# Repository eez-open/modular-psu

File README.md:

### Ownership and License
The contributors are listed in CONTRIB.TXT. 

Licenses | OSHWA UID
--|--
 | 

### Introduction

EEZ Bench Box 3 (BB3) represents a new category of *modular* Test and Measurement (T&M) equipment. It provides a complete open-source hardware and software framework that bridges the gap between – and combines the best features of – DIY hobbyist tools and professional benchtop equipment. 
BB3 was inspired by the [EEZ H24005](https://github.com/eez-open/psu-hw) power supply project ([OSHWA UID HR000001](https://certification.oshwa.org/hr000001.html)), which attracted many enthusiasts with its broad feature-set, rich user interface, DIY-friendliness, and fully open-source design. 
It initially comes with two DC power modules (hence the name of repository *modular-psu*) and will be expanded with new T&M modules (e.g. multi-channel power source, 2/4-quadrant power module, multi-channel temperature sensor module, data logger, switch matrix, digital I/O expander, function generator, data acquisition module, etc.). 
BB3 is made up of the following components:

* _[BP3C](https://github.com/eez-open/modular-psu/tree/master/bp3c)_ EEZ DIB backplane with power output coupling capability of first two modules
* _[AUX power supply](https://github.com/eez-open/modular-psu/tree/master/aux-ps)_ board with AC input protection, soft-start/power-up control, DC fan controller and +5 V / +12 V power outputs
* _[MCU](https://github.com/eez-open/modular-psu/tree/master/mcu)_ board based on STM32F769IIT6 32-bit ARM Cortex-M7
* _[DCP405](https://github.com/eez-open/modular-psu/tree/master/dcp405)_, 0 - 40 V / 50 mA / 5 A DC power source module
* _[DCM224](https://github.com/eez-open/dib-dcm224)_, dual sync buck 1 - 24 V / max. 4.9 A module (**retired**)
* _[Metal enclosure](https://github.com/eez-open/modular-psu/tree/master/enclosure)_ for housing up to 3 modules with 4.3" TFT LCD. Dimensions: 290 (W) x 123 (H) x 240 (D) mm

### Supported technologies

* _EEZ Flow_ (Visual programming tool for test and measurement automation)
* SCPI (Reference Guide in [PDF](https://github.com/eez-open/modular-psu-firmware/blob/master/docs/SCPI%20reference%20guide/EEZ%20BB3%20SCPI%20reference%20guide.pdf))
* MicroPython (script [examples](https://github.com/eez-open/modular-psu-firmware/tree/master/scripts), an example [video](https://www.youtube.com/watch?v=I0y6fgv8G00))
* MQTT (an intro [video](https://www.youtube.com/watch?v=THyfLSSAhrI))
* Node-RED integration (an intro [video](https://www.youtube.com/watch?v=0xQ6Xuq53fA))

### Other DIB modules

* [MIO168](https://github.com/eez-open/dib-mio168) Mixed I/O module
* [PREL6](https://github.com/eez-open/dib-prel6) power relays module
* [SMX46](https://github.com/eez-open/dib-smx46) programmable switch matrix module
* [MUX14D](https://github.com/eez-open/dib-mux14d) dual 7:1 reed relay 2-wire multiplexer

### Related topics and links

* EEZ BB3 [firmware](https://github.com/eez-open/modular-psu-firmware)
* [EEZ Studio](https://www.envox.eu/studio/studio-introduction)
* EEZ [DIB v1.2](https://github.com/eez-open/modular-psu/tree/master/DIB) specification
* EEZ DIB peripheral modules [KiCad 8.x project template](https://github.com/eez-open/dib-kicad-template)
* [Discord](https://discord.gg/dhYMnCB) server
* [X](https://x.com/envox) (ex Twitter)
* [YouTube](https://www.youtube.com/c/eezopen) channel
* [EEVblog forum](https://www.eevblog.com/forum/projects/eez-h25005-a-possible-successor-of-eez-h24005-programmable-power-supply/) discussion
* [Crowd Supply](https://www.crowdsupply.com/envox/eez-bb3) crowdfunding landing page
* [EMC certificate](https://www.envox.eu/?smd_process_download=1&download_id=2806), [LVD cerificate](https://www.envox.eu/?smd_process_download=1&download_id=2808)
* [Sigrok](https://sigrok.org/wiki/Envox_EEZ_Bench_Box_3)
* [Liberpay](https://liberapay.com/eez-open/donate) donations 

### Where to buy?

* [EEZ Web store](https://www.envox.eu/store) (out of stock)
* [Mouser](https://www.mouser.com/Search/Refine?Keyword=cs-bb3-) (kit only, excl. EU/UK)
* [Crowd supply](https://www.crowdsupply.com/envox/eez-bb3) (kit only, excl. EU/UK)

### Security & Regulatory Compliance

* [CRA Compliance Documentation](./security/README.md)

---
Please note that some previous board types and revisions that could be still usable in some cases can be found under *[previous design](https://github.com/eez-open/modular-psu/tree/master/previous%20designs)* folder.

### Notes on Shell Syntax (Community Feedback)
In shell scripting, the syntax used for loops can impact portability and readability across different environments.
Potential Issue with Braces:

 while (( i++ < 10 )) { echo i is $i } 
 
may not work reliably in all shell environments. For instance, in Zsh, this syntax will fail unless SHORT_LOOPS is explicitly enabled.
It can also cause issues with syntax highlighting and script execution.

* Alternate Approach: To ensure broader compatibility and clearer syntax, prefer the standard do ... done block structure:

i=0
while (( i++ < 10 ))
do
 echo "i is $i"
done

This format is - Compatible with most POSIX-compliant shells (e.g., Bash, Zsh, etc.) and Syntax-highlight friendly in editors and IDEs.

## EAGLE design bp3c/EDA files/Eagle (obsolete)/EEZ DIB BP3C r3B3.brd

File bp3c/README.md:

EEZ DIB BP3C is backplane for connecting up to three EEZ DIB peripheral modules. When power modules (e.g. [DCP405](https://github.com/eez-open/modular-psu/tree/master/dcp405)) are plugged into slot #1 and #2, their outputs can be combined under firmware control in one of the following way:

- Serial coupling to double max. output voltage 
- Parallel coupling to double max. output current
- Ch#1 `Out-` and Ch#2 `Out+` coupling for split rail output

Additionaly, it is possible to couple `Out-` terminals of all installed power modules (common GND).

The BP3C backplane provides dedicated BOOT output for each peripheral module that comes with on-board MCU and which firmware could be uploaded via SPI or UART. Programmable reset output is also featured that firmware upload procedure can be initiated without power recycling.

Dimensions: 110 x 90 mm, 2-layer PCB

### KiCad project (v7 or newer)

* [BP3C r3B3](https://github.com/eez-open/modular-psu/tree/master/bp3c/EDA%20files/KiCad)

All symbols, footprints and 3D models used in the project can be found in the [EEZ-DIB Library](https://github.com/eez-open/eez-kicad-libraries) plugin for KiCad.

### Bill of materials

* [Download](https://github.com/eez-open/modular-psu/blob/master/bp3c/EDA%20files/KiCad/bom/ibom.html) as raw file _Interactive BOM_ (ibom.html) and open it locally in your browser.

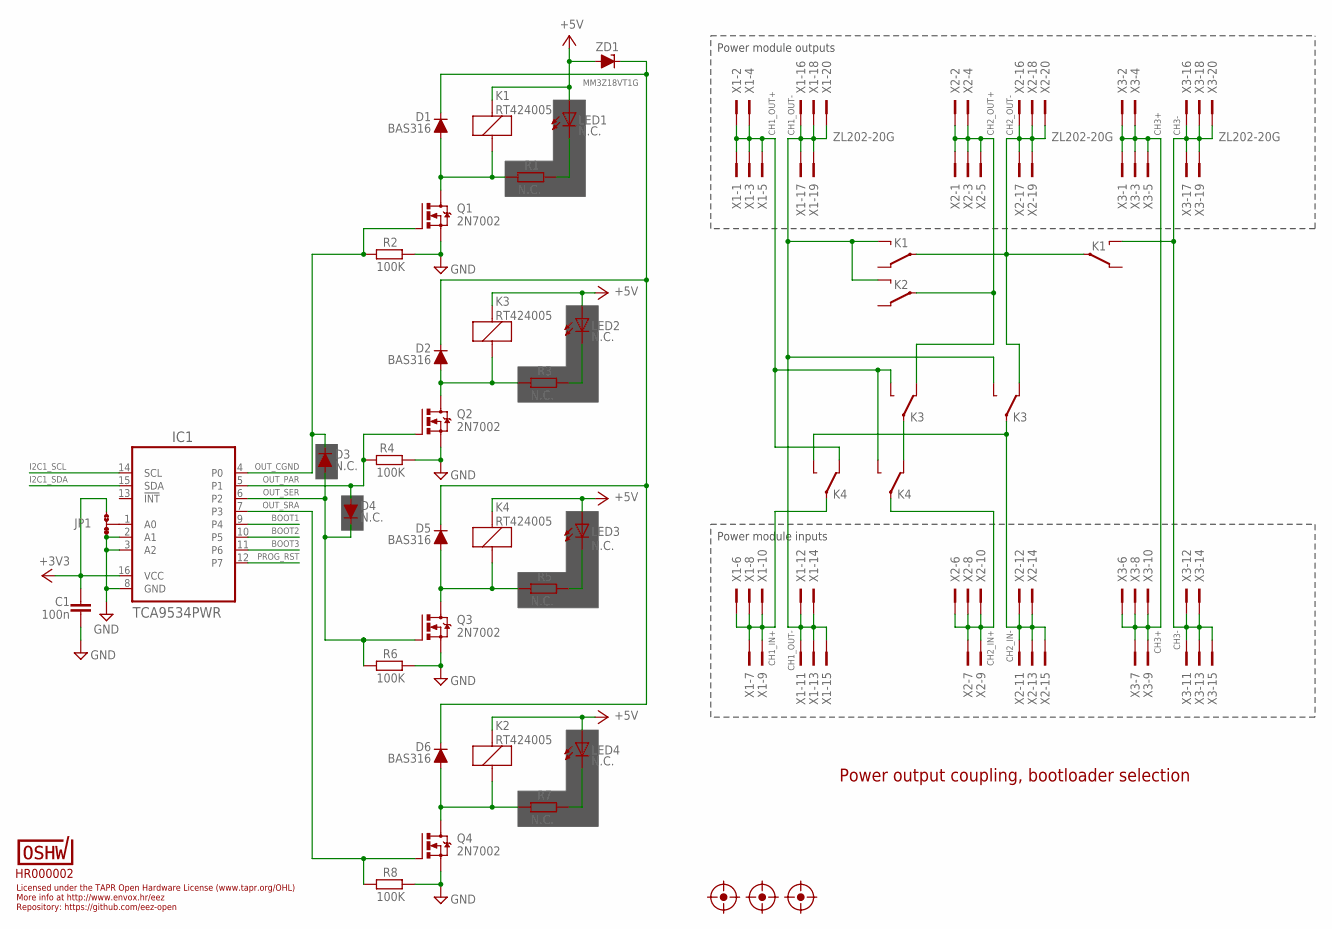
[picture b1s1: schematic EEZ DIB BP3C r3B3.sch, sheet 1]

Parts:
C1: 100n; C0603
D1, D2, D5, D6: BAS316; SOD323-R
D3, D4: N.C.; SOD323-R
FM1, FM2, FM3: FIDUCIAL
IC1: TCA9534PWR; PW(R-PDSO-G16)
JP1: JP3-CUT
K1, K2, K3, K4: RT424005; RT-C/016A5_ROUND
LABEL1: HR000002; CERT-SMALL-SILK
LED1, LED2, LED3, LED4: N.C.; LED_0805
Q1, Q2, Q3, Q4: 2N7002; SOT103P240X110-3N; MPN 2N7002-7-F
R1, R3, R5, R7: N.C.; R0805
R2, R4, R6, R8: 100K; R0805
X1, X2, X3: ZL202-20G; DS1021-2*10SF11
ZD1: MM3Z18VT1G; SOD323-R

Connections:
+3V3: C1.1, IC1.16 (VCC), JP1.NO; also elsewhere on the board
+5V: K1.A2 (C1), K2.A2 (C1), K3.A2 (C1), K4.A2 (C1), LED1.A, LED2.A, LED3.A, LED4.A, ZD1.A; also elsewhere on the board
BOOT1: IC1.9 (P4); also elsewhere on the board
BOOT2: IC1.10 (P5); also elsewhere on the board
BOOT3: IC1.11 (P6); also elsewhere on the board
CH1_IN+: K4.11A, X1.6, X1.7, X1.8, X1.9, X1.10
CH1_OUT+: K3.14A (O), K4.12A (S), K4.14B (O), X1.1, X1.2, X1.3, X1.4, X1.5
CH1_OUT-: K1.14A (O), K2.14A (O), K3.14B (O), X1.11, X1.12, X1.13, X1.14, X1.15, X1.16, X1.17, X1.18, X1.19, X1.20
CH2_IN+: K4.11B, X2.6, X2.7, X2.8, X2.9, X2.10
CH2_IN-: K3.11B, K4.14A (O), X2.11, X2.12, X2.13, X2.14, X2.15
CH2_OUT+: K2.11A, K3.12A (S), X2.1, X2.2, X2.3, X2.4, X2.5
CH2_OUT-: K1.11A, K1.11B, K3.12B (S), X2.16, X2.17, X2.18, X2.19, X2.20
CH3+: X3.1, X3.2, X3.3, X3.4, X3.5, X3.6, X3.7, X3.8, X3.9, X3.10
CH3-: K1.14B (O), X3.11, X3.12, X3.13, X3.14, X3.15, X3.16, X3.17, X3.18, X3.19, X3.20
GND: C1.2, IC1.2 (A1), IC1.3 (A2), IC1.8 (GND), JP1.NC, Q1.2 (S), Q2.2 (S), Q3.2 (S), Q4.2 (S), R2.1, R4.1, R6.1, R8.1; also elsewhere on the board
I2C1_SCL: IC1.14 (SCL); also elsewhere on the board
I2C1_SDA: IC1.15 (SDA); also elsewhere on the board
unnamed: LED3.C, R5.1
unnamed: LED2.C, R3.1
unnamed: IC1.1 (A0), JP1.COM
unnamed: D1.C, D2.C, D5.C, D6.C, ZD1.C
unnamed: D1.A, K1.A1 (C2), Q1.3 (D), R1.2
unnamed: LED1.C, R1.1
unnamed: D6.A, K2.A1 (C2), Q4.3 (D), R7.2
unnamed: LED4.C, R7.1
unnamed: D5.A, K4.A1 (C2), Q3.3 (D), R5.2
unnamed: D2.A, K3.A1 (C2), Q2.3 (D), R3.2
OUT_CGND: D3.C, IC1.4 (P0), Q1.1 (G), R2.2
OUT_PAR: D4.A, IC1.5 (P1), Q2.1 (G), R4.2
OUT_SER: D3.A, D4.C, IC1.6 (P2), Q3.1 (G), R6.2
OUT_SRA: IC1.7 (P3), Q4.1 (G), R8.2
PROG_RST: IC1.12 (P7); also elsewhere on the board
SER_PAR: K3.11A, K4.12B (S)

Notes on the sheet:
Licensed under the TAPR Open Hardware License (www.tapr.org/OHL)
Repository: https://github.com/eez-open
More info at http://www.envox.hr/eez
Power output coupling, bootloader selection
Power module inputs
Power module outputs

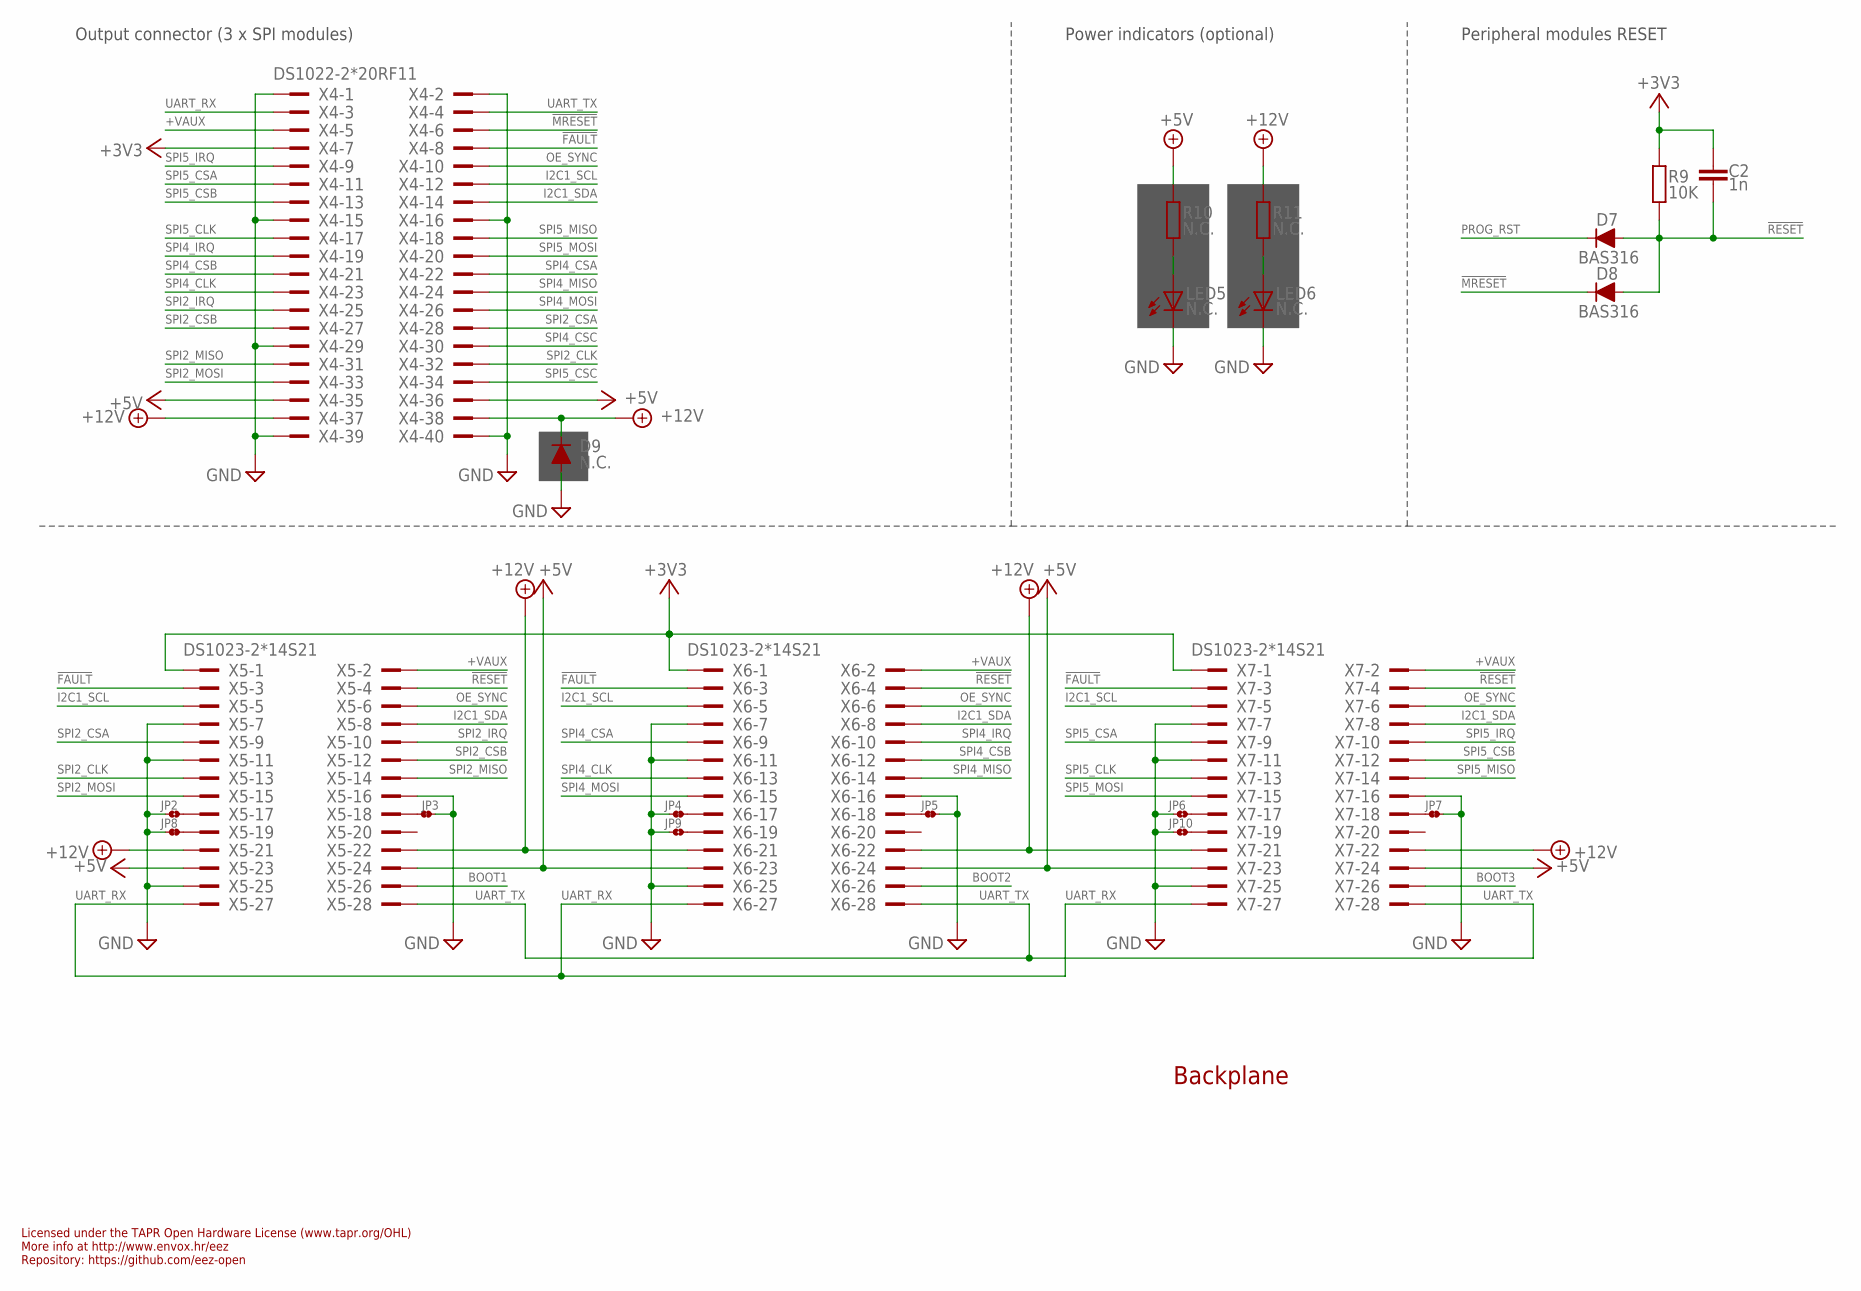
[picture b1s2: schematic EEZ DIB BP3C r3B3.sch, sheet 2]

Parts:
C2: 1n; C0805
D7, D8: BAS316; SOD323-R
D9: N.C.; DO214AA
JP2, JP6, JP9, JP10: JP2-CUT
JP3, JP4, JP5, JP7, JP8: JP2-NOCUT
LED5, LED6: N.C.; LED_0805
R9: 10K; R0805
R10, R11: N.C.; R0805
X4: DS1022-2*20RF11; ZL212-40KG
X5, X6, X7: DS1023-2*14S21; TSW-114-07-F-D

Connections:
!FAULT: X4.8, X5.3, X6.3, X7.3
!MRESET: D8.C, X4.6
!RESET: C2.1, D7.A, D8.A, R9.2, X5.4, X6.4, X7.4
+3V3: C2.2, R9.1, X4.7, X5.1, X6.1, X7.1; also elsewhere on the board
+5V: R10.1, X4.35, X4.36, X5.23, X5.24, X6.23, X6.24, X7.23, X7.24; also elsewhere on the board
+12V: D9.C, R11.1, X4.37, X4.38, X5.21, X5.22, X6.21, X6.22, X7.21, X7.22
+VAUX: X4.5, X5.2, X6.2, X7.2
BOOT1: X5.26; also elsewhere on the board
BOOT2: X6.26; also elsewhere on the board
BOOT3: X7.26; also elsewhere on the board
GND: D9.A, JP2.1, JP3.2, JP4.1, JP5.2, JP6.1, JP7.2, JP8.1, JP9.1, JP10.1, LED5.C, LED6.C, X4.1, X4.2, X4.15, X4.16, X4.29, X4.39, X4.40, X5.7, X5.11, X5.16, X5.25, X6.7, X6.11, X6.16, X6.25, X7.7, X7.11, X7.16, X7.25; also elsewhere on the board
I2C1_SCL: X4.12, X5.5, X6.5, X7.5; also elsewhere on the board
I2C1_SDA: X4.14, X5.8, X6.8, X7.8; also elsewhere on the board
unnamed: JP3.1, X5.18
unnamed: LED5.A, R10.2
unnamed: LED6.A, R11.2
unnamed: JP2.2, X5.17
unnamed: JP8.2, X5.19
unnamed: JP5.1, X6.18
unnamed: JP4.2, X6.17
unnamed: JP9.2, X6.19
unnamed: JP7.1, X7.18
unnamed: JP6.2, X7.17
unnamed: JP10.2, X7.19
OE_SYNC: X4.10, X5.6, X6.6, X7.6
PROG_RST: D7.C; also elsewhere on the board
SPI2_CLK: X4.32, X5.13
SPI2_CSA: X4.28, X5.9
SPI2_CSB: X4.27, X5.12
SPI2_IRQ: X4.25, X5.10
SPI2_MISO: X4.31, X5.14
SPI2_MOSI: X4.33, X5.15
SPI4_CLK: X4.23, X6.13
SPI4_CSA: X4.22, X6.9
SPI4_CSB: X4.21, X6.12
SPI4_CSC: X4.30
SPI4_IRQ: X4.19, X6.10
SPI4_MISO: X4.24, X6.14
SPI4_MOSI: X4.26, X6.15
SPI5_CLK: X4.17, X7.13
SPI5_CSA: X4.11, X7.9
SPI5_CSB: X4.13, X7.12
SPI5_CSC: X4.34
SPI5_IRQ: X4.9, X7.10
SPI5_MISO: X4.18, X7.14
SPI5_MOSI: X4.20, X7.15
UART_RX: X4.3, X5.27, X6.27, X7.27
UART_TX: X4.4, X5.28, X6.28, X7.28

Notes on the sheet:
Licensed under the TAPR Open Hardware License (www.tapr.org/OHL)
Repository: https://github.com/eez-open
More info at http://www.envox.hr/eez
Backplane
Output connector (3 x SPI modules)
Power indicators (optional)
Peripheral modules RESET

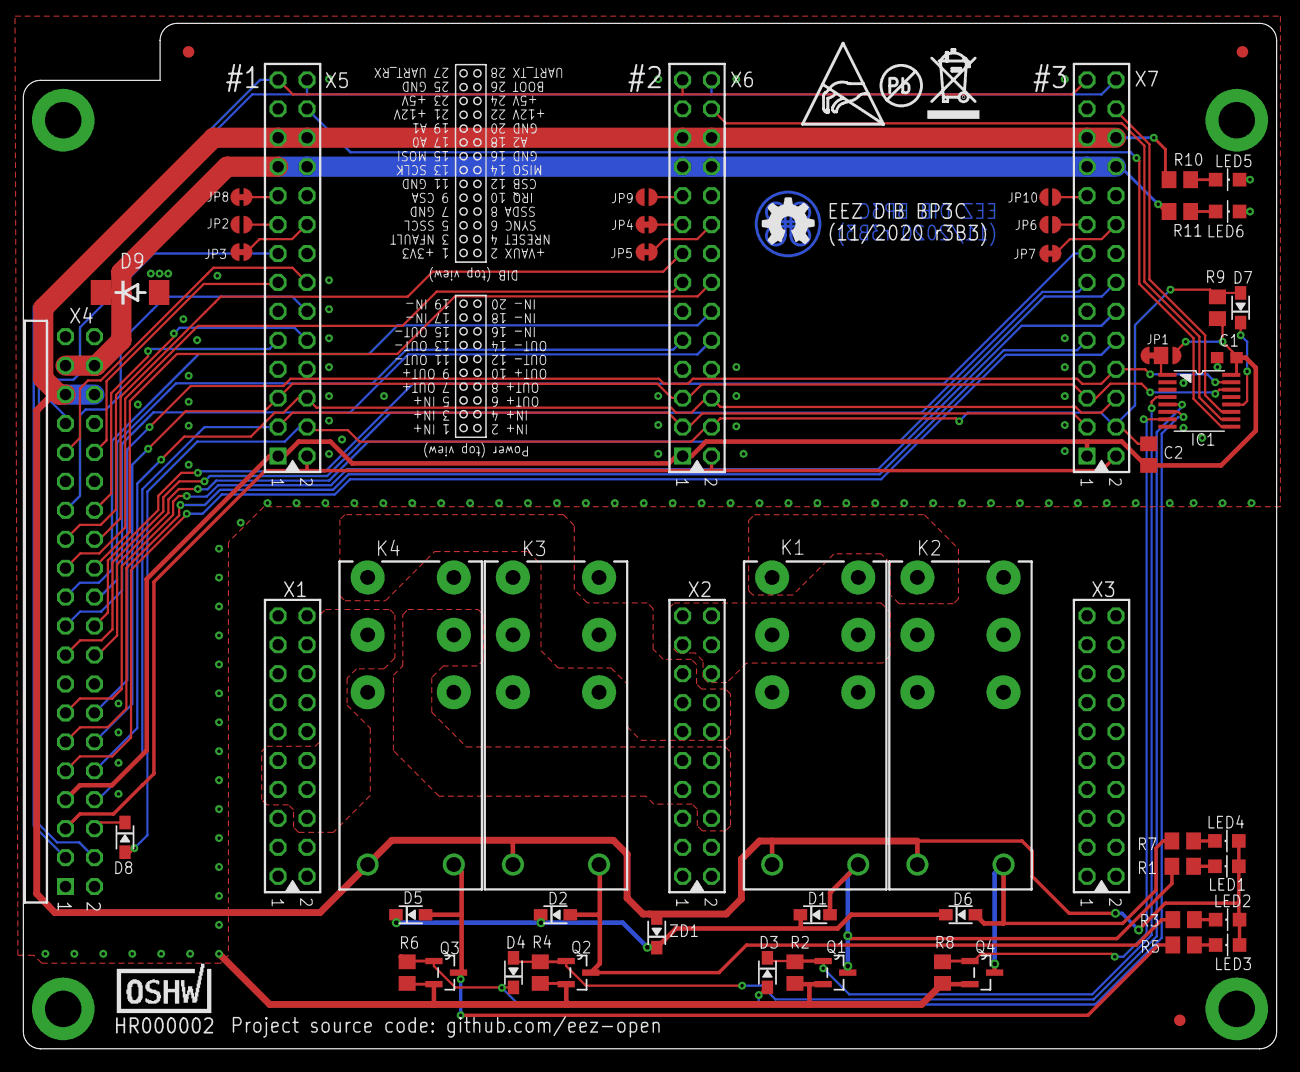
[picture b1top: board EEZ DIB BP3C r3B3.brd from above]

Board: 2 copper layers, 110.0 x 90.0 mm, 63 parts (0 on the bottom side), 70 nets.

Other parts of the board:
EEZ_SIGNATURE: SIGNATURESMALL; SIGNATURE_5MM
U$2: RECYCLE_BIN1/8
U$4: ESD_SYMBOL
U$5: PB_SMALL

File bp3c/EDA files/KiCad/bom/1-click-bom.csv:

References,Qty,Description,Digikey,Mouser,TME
C1,1,100n,1276-1005-2-ND,187-CL10B104KO8NNNC ,CL10B104KA8NNNC
C2,1,1n,732-7858-1-ND ,710-885012007040 ,CL21C102JBCNNNC
"R1, R2, R3, R4",4,100K,RMCF0805FT100KCT-ND ,71-CRCW0805100KFKEAC,SMD0805-100K-1%
R11,1,10K,311-10.0KCRCT-ND,603-RC0805FR-0710KL,RC0805FR-0710K
"D3, D4, D5, D6, D8, D9",6,BAS316,1727-7370-1-ND,771-BAS316-T/R,"BAS316,115"
"X1, X2, X3",3,77313-802-20LF,609-77313-802-20LF-ND,649-77313-802-20LF,DS1021-2*10SF11
"X4, X6, X7",3,DS1023-2*14S21,S7082-ND ,SSQ-114-01-T-D,DS1023-2*14S21
X5,1,68020-140HLF,68020-140HLF-ND,649-68020-140HLF ,DS1022-2*20RF11
"K1, K2, K3, K4",4,RT424005,PB1998-ND,655-RT424005 ,RT424005
"Q1, Q2, Q3, Q4",4,2N7002,T2N7002AKLMCT-ND,757-T2N7002AKLM,2N7002LT1G
IC1,1,TCA9534PWR,296-40574-1-ND ,595-TCA9534PWR,TCA9534PWR
ZD1,1,MM3Z18VT1G,MM3Z18VT1GOSCT-ND,863-MM3Z18VT1G,MM3Z18VT1G

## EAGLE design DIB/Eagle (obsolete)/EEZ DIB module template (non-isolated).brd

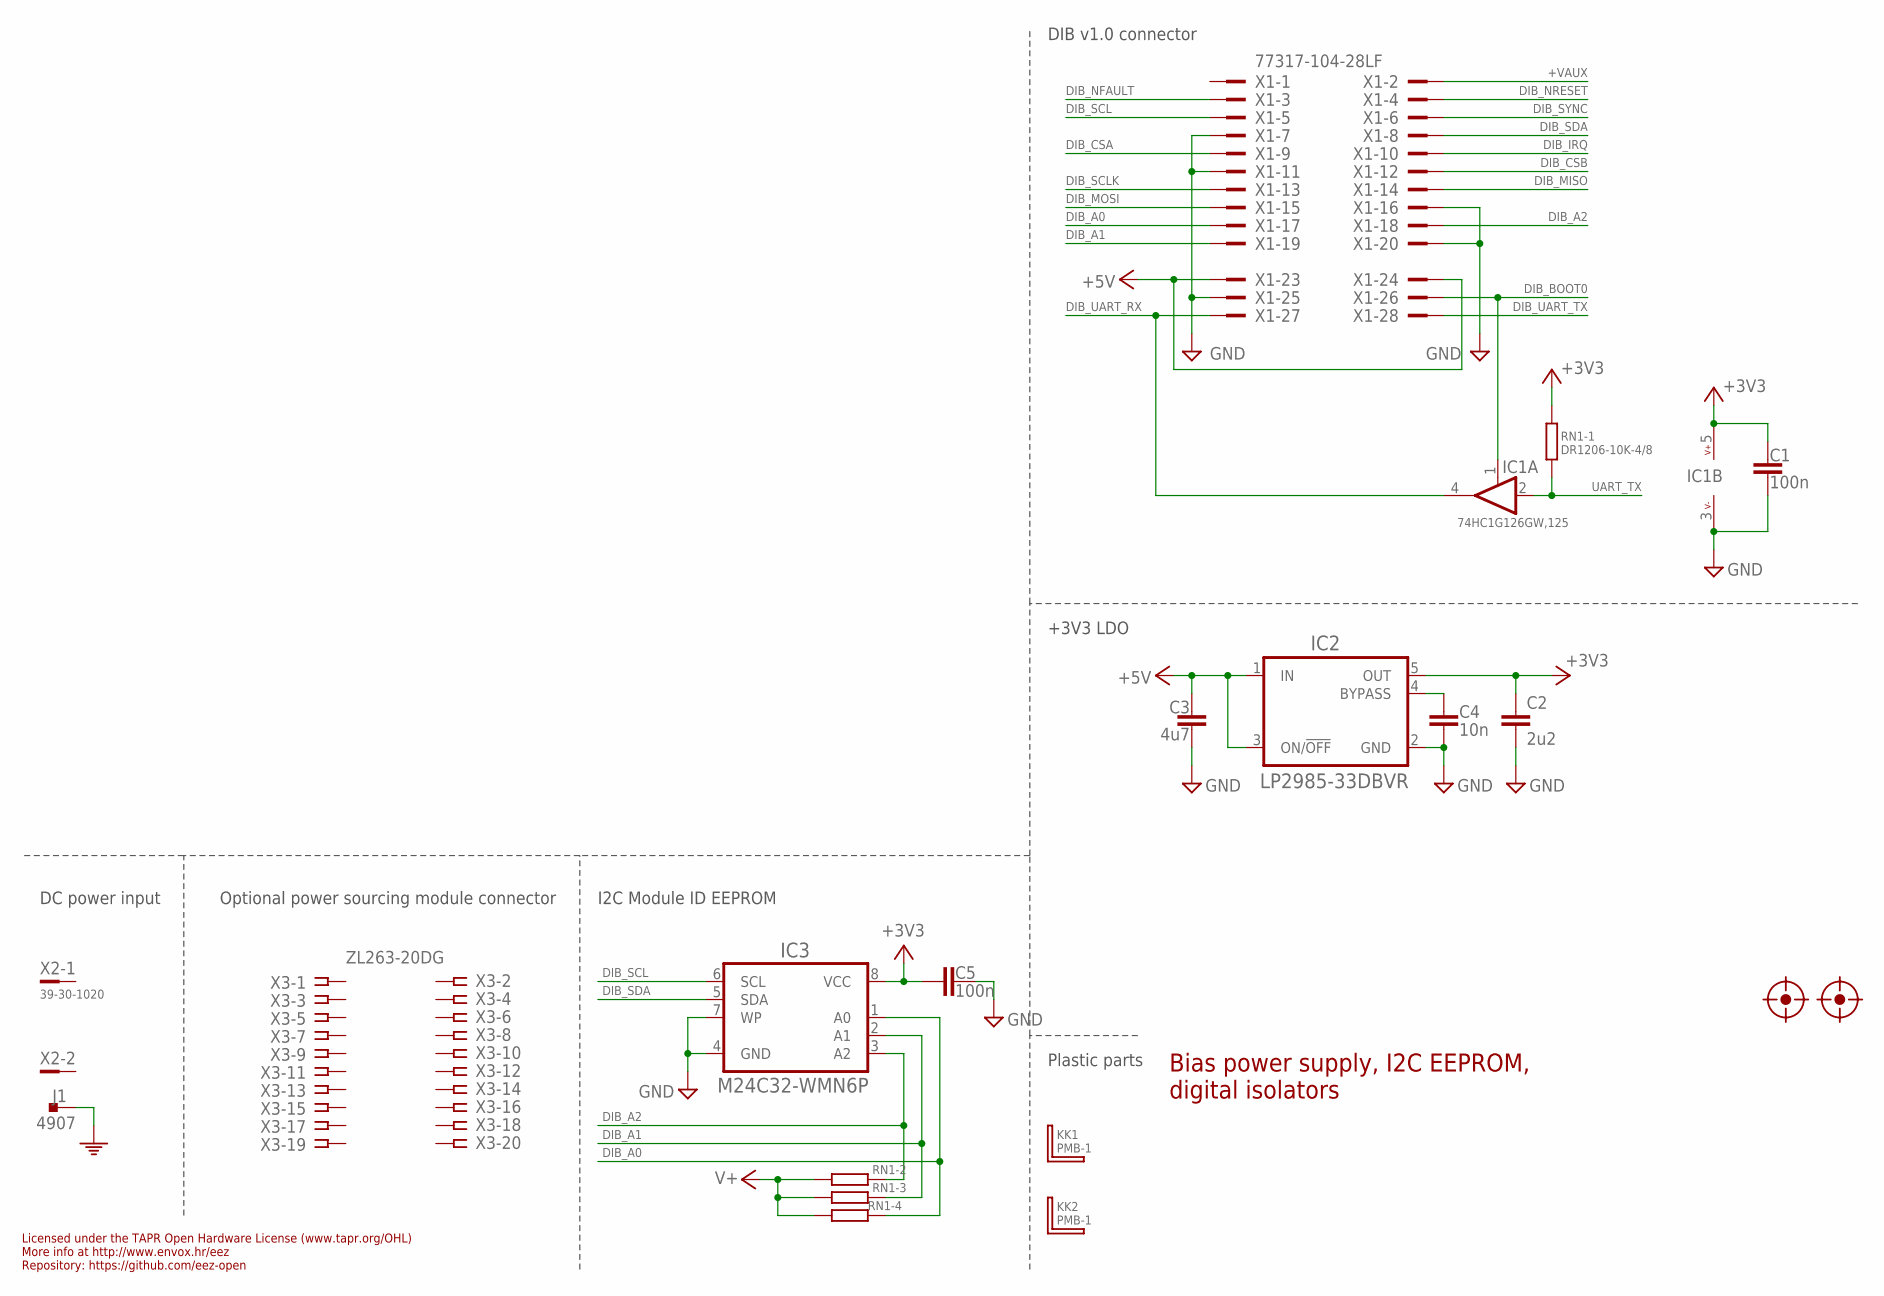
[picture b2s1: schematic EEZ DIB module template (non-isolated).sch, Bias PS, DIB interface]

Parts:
C1, C5: 100n; C0603
C2: 2u2; C0805
C3: 4u7; C0805
C4: 10n; C0805
FM1, FM2: FIDUCIAL_2; FIDUCIAL_DUAL
IC1: 74HC1G126GW,125; SOT65P210X110-5N
IC2: LP2985-33DBVR; SOT95P270X145-5N
IC3: M24C32-WMN6P; SOIC127P600X173-8N
J1: 4907; PCB_TAB-4907
KK1, KK2: PMB-1; PCB-MB
RN1: DR1206-10K-4/8; CAY16
X1: 77317-104-28LF
X2: 39-30-1020; MINIFIT_39301020
X3: ZL263-20DG; SSW-110-02-T-D-RA

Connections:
+3V3: C1.1, C2.1, C5.2, IC1.5 (V+), IC2.5 (OUT), IC3.8 (VCC), RN1.8 (2)
+5V: C3.2, IC2.1 (IN), IC2.3 (ON/!OFF), X1.23, X1.24
+VAUX: X1.2
DIB_A0: IC3.1 (A0), RN1.4 (1), X1.17
DIB_A1: IC3.2 (A1), RN1.3 (1), X1.19
DIB_A2: IC3.3 (A2), RN1.2 (1), X1.18
DIB_BOOT0: IC1.1 (EN), X1.26
DIB_CSA: X1.9
DIB_CSB: X1.12
DIB_IRQ: X1.10
DIB_MISO: X1.14
DIB_MOSI: X1.15
DIB_NFAULT: X1.3
DIB_NRESET: X1.4
DIB_SCL: IC3.6 (SCL), X1.5
DIB_SCLK: X1.13
DIB_SDA: IC3.5 (SDA), X1.8
DIB_SYNC: X1.6
DIB_UART_RX: IC1.4 (O), X1.27
DIB_UART_TX: X1.28
GND: C1.2, C2.2, C3.1, C4.1, C5.1, IC1.3 (V-), IC2.2 (GND), IC3.4 (GND), IC3.7 (WP), X1.7, X1.11, X1.16, X1.20, X1.25
unnamed: C4.2, IC2.4 (BYPASS)
PE: J1.1, J1.2
UART_TX: IC1.2 (I), RN1.1
V+: RN1.5 (2), RN1.6 (2), RN1.7 (2)

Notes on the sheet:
Licensed under the TAPR Open Hardware License (www.tapr.org/OHL)
Repository: https://github.com/eez-open
More info at http://www.envox.hr/eez
I2C Module ID EEPROM
Bias power supply, I2C EEPROM, digital isolators
Plastic parts
DIB v1.0 connector
DC power input
Optional power sourcing module connector
+3V3 LDO

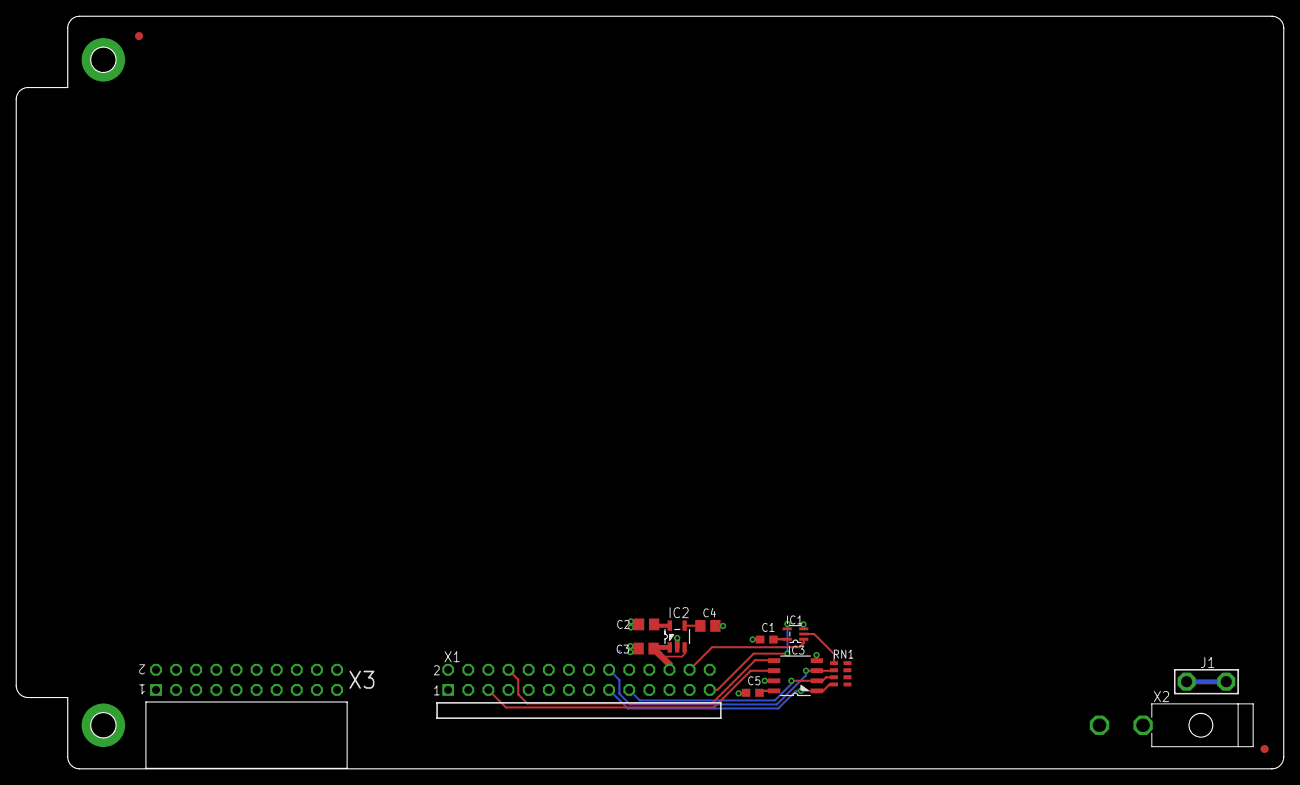
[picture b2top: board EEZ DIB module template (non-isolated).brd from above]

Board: 4 copper layers, 160.0 x 95.0 mm, 17 parts (0 on the bottom side), 14 nets.

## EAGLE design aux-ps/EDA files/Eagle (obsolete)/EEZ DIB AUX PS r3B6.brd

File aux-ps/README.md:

### Overview

_IMPORTANT: A crowdfunded version of the AUX-PS (r3B3) can be found [here](https://github.com/eez-open/modular-psu/tree/master/previous%20designs/aux-ps%20r3B3%20(Crowd%20Supply%20edition))._

AUX Power supply board for powering MCU board and backplane. It includes fan controller and AC power control with softstart (inrush current limiter) for power modules like DCP405 and DCM224.

### Feature list

* On-board IEC C14 AC inlet with dual 20 x 5 mm fuses
* On-board AC power switch
* AC input protection (SAR, MOV)
* AC input filter for EMI compliance
* 3 x AC power outputs
* Soft-start/standby relay control
* +5 V, 10 W (optional 20 W)
* +12 V, 10 W
* I2C DC fan controller with temperature sensor and speed control
* Two 3-wire or 4-wire 12V DC fans (standard PC fan pinout)
* Standby LED indictor
* On-board PE 4 mm terminal
* AC mains frequency detection (optional)
* Dimensions: 230.5 x 60 mm, 2-layer PCB
* **CE certified design**

### KiCad project (v7 or newer)

* [AUX-PS r3B7](https://github.com/eez-open/modular-psu/tree/master/aux-ps/EDA%20files/KiCad)

All symbols, footprints and 3D models used in the project can be found in the [EEZ-DIB Library](https://github.com/eez-open/eez-kicad-libraries) plugin for KiCad.

### Bill of materials

* [Download](https://github.com/eez-open/modular-psu/blob/master/aux-ps/EDA%20files/KiCad/bom/ibom.html) as raw file _Interactive BOM_ (ibom.html) and open it locally in your browser.

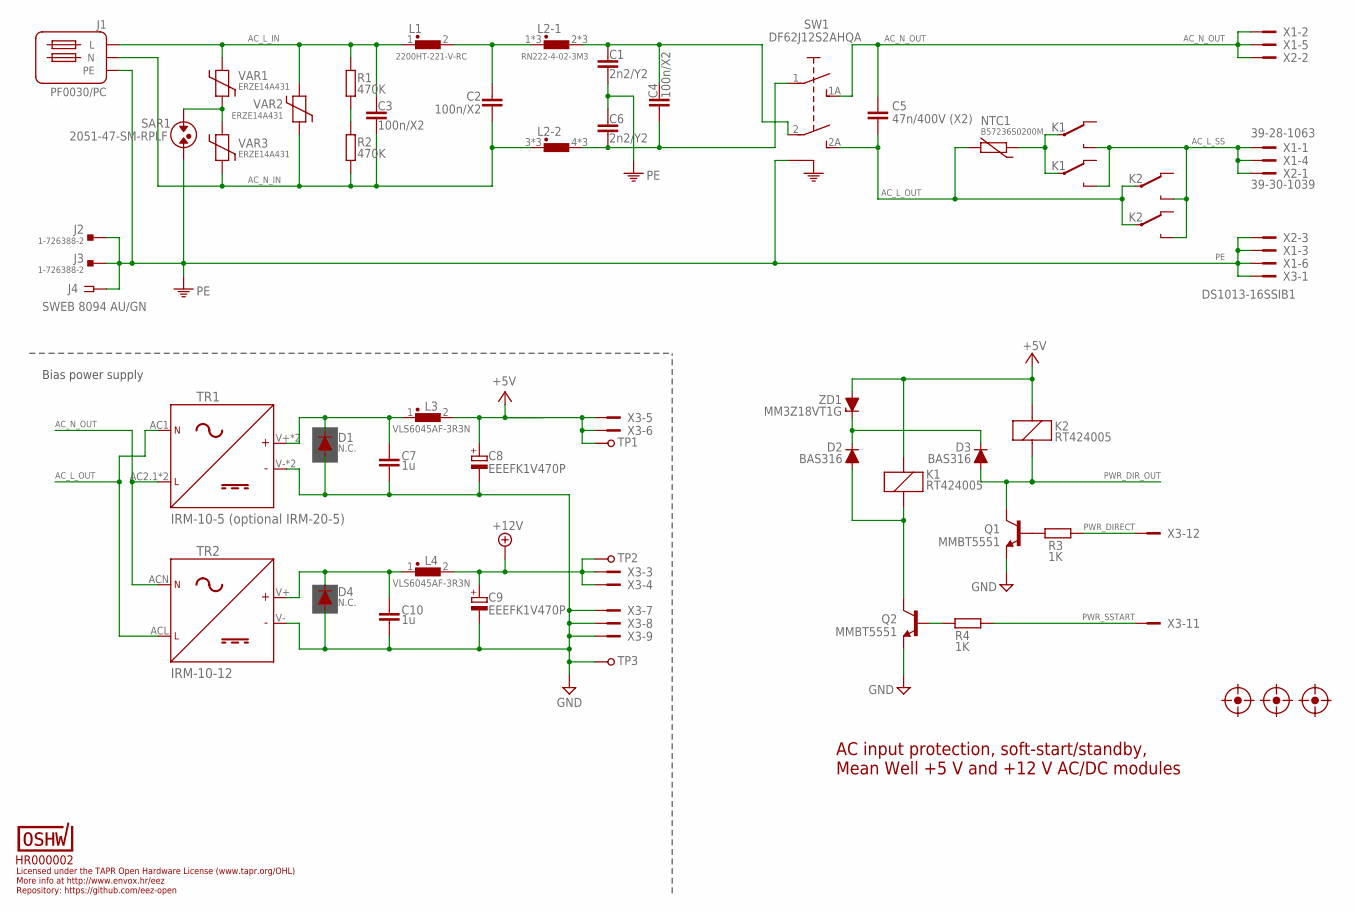
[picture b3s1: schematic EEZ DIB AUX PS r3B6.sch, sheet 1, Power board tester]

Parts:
C1, C6: 2n2/Y2; C075-042X103
C2, C3, C4: 100n/X2; C150-054X183
C5: 47n/400V (X2); C102-054X133
C7, C10: 1u; C0805
C8, C9: EEEFK1V470P; CAPAE660X610N
D1, D4: N.C.; DO214AA
D2, D3: BAS316; SOD323-R
FM1, FM2, FM3: FIDUCIAL
J1: PF0030/PC
J2, J3: 1-726388-2; PCB_TAB-4.8MM
J4: SWEB 8094 AU/GN; S16N-PC
K1, K2: RT424005; RT-C/016A5_ROUND
L1: 2200HT-221-V-RC; BOURNS_2200
L2: RN222-4-02-3M3; BOURNS_7100_COMBO
L3, L4: VLS6045AF-3R3N; COILCRAFT_HPI0630
LABEL1: HR000002; CERT-SMALL-SILK
NTC1: B57236S0200M; NTC_11.5X6_RM5
Q1, Q2: MMBT5551; SOT23-BEC
R1, R2: 470K; R1206
R3, R4: 1K; R0805
SAR1: 2051-47-SM-RPLF; SAR_4.5MM
SW1: DF62J12S2AHQA; DF62J12S2
TP1, TP2, TP3: PCB_TEST_TABSHIELD; PCB_SHIELD_TAB
TR1: IRM-10-5 (optional IRM-20-5); IRM-10/20_COMBO
TR2: IRM-10-12; IRM-10
VAR1, VAR2, VAR3: ERZE14A431; VARISTOR_16MM
X1: 39-28-1063; MINIFIT_5566-06A_CRE
X2: 39-30-1039; MINIFIT_39301039_CRE
X3: DS1013-16SSIB1; IDC-16PIN
ZD1: MM3Z18VT1G; SOD323-R

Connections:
+5V: C8.1 (+), K1.A2 (C1), K2.A1 (C2), L3.2, TP1.1, X3.5, X3.6, ZD1.A; also elsewhere on the board
+12V: C9.1 (+), L4.2, TP2.1, X3.3, X3.4; also elsewhere on the board
AC_L_IN: C3.1, J1.L, L1.1, R1.2, VAR1.2, VAR2.1
AC_L_OUT: C5.2, K2.11A, K2.11B, NTC1.1, SW1.2A (S1), TR1.AC1 (AC/N), TR2.ACL (AC/L); also elsewhere on the board
AC_L_RTC: C1.1, C4.2, L2.2, L2.2A (2), L2.2B (2), SW1.2 (P1)
AC_L_SS: K1.14A (O), K1.14B (O), K2.14A (O), K2.14B (O), X1.1, X1.4, X2.1
AC_N_IN: C2.2, C3.2, J1.N, L2.3 (1), L2.3A (1), L2.3B (1), R2.1, VAR2.2, VAR3.1
AC_N_OUT: C5.1, SW1.1A (S), TR1.AC2.1 (AC/L), TR1.AC2.2 (AC/L), TR2.ACN (AC/N), X1.2, X1.5, X2.2; also elsewhere on the board
AC_N_RTC: C4.1, C6.2, L2.4 (2), L2.4A (2), L2.4B (2), SW1.1
GND: C7.2, C8.2 (-), C9.2 (-), C10.2, D1.A, D4.A, Q1.E, Q2.E, TP3.1, TR1.V- (-), TR1.V-1 (-), TR2.V- (-), X3.7, X3.8, X3.9; also elsewhere on the board
unnamed: R1.1, R2.2
unnamed: C2.1, L1.2, L2.1, L2.1A (1), L2.1B (1)
unnamed: SAR1.1, VAR1.1, VAR3.2
unnamed: K1.11A, K1.11B, NTC1.2
unnamed: C10.1, D4.C, L4.1, TR2.V+ (+)
unnamed: D2.C, D3.C, ZD1.C
unnamed: Q2.B, R4.1
unnamed: C7.1, D1.C, L3.1, TR1.V+ (+), TR1.V+1 (+)
unnamed: D2.A, K1.A1 (C2), Q2.C
unnamed: Q1.B, R3.1
PE: C1.2, C6.1, J1.PE, J2.1, J2.2, J3.1, J3.2, J4.1, J4.NC1, J4.NC2, J4.NC3, J4.NC4, SAR1.2, SW1.PE1 (PE), SW1.PE2 (PE), X1.3, X1.6, X2.3, X3.1
PWR_DIRECT: R3.2, X3.12
PWR_DIR_OUT: D3.A, K2.A2 (C1), Q1.C; also elsewhere on the board
PWR_SSTART: R4.2, X3.11

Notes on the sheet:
Licensed under the TAPR Open Hardware License (www.tapr.org/OHL)
Repository: https://github.com/eez-open
More info at http://www.envox.hr/eez
AC input protection, soft-start/standby, Mean Well +5 V and +12 V AC/DC modules
Bias power supply

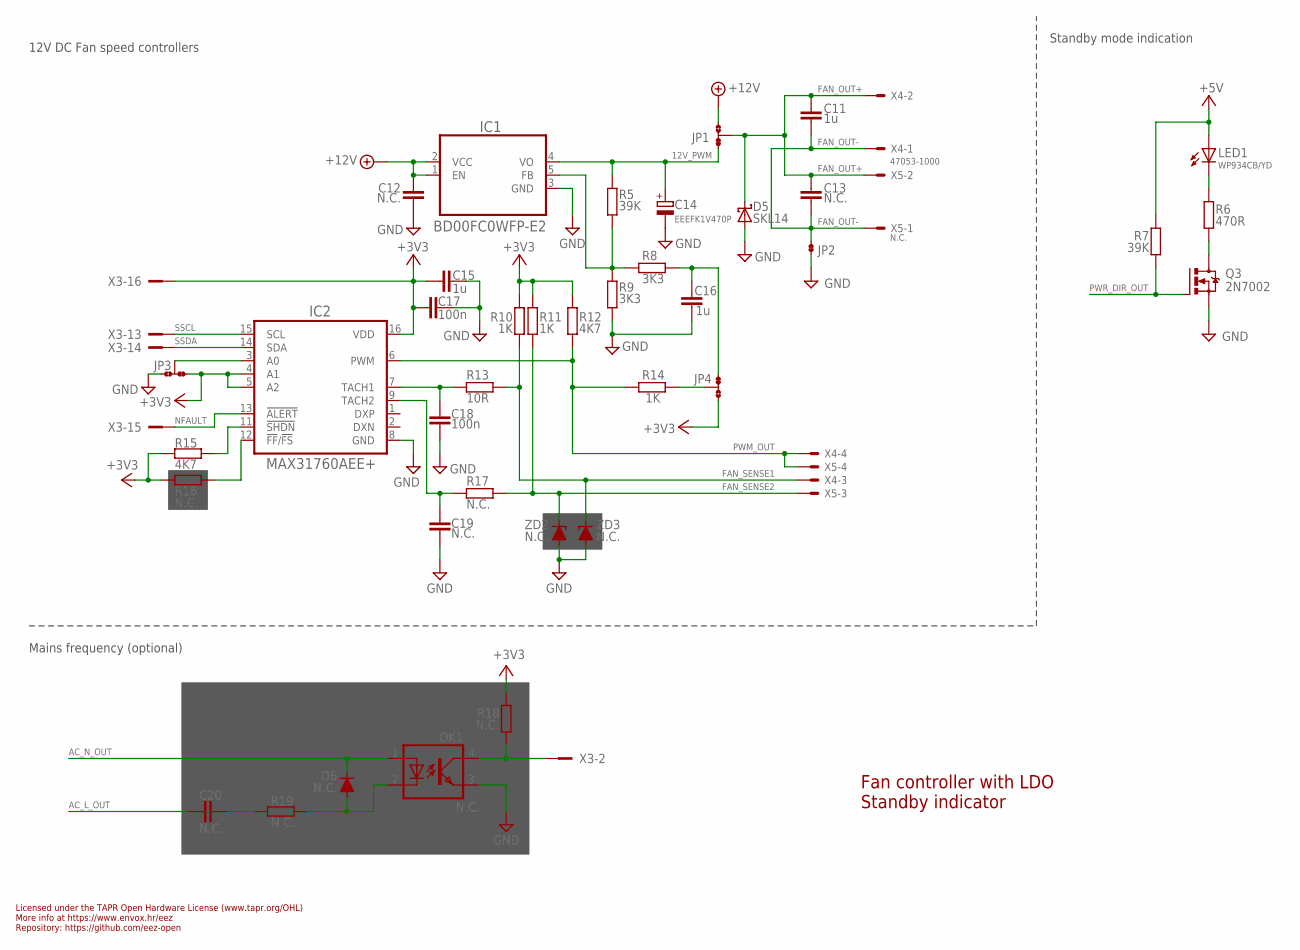
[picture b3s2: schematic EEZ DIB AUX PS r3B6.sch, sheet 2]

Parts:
C11, C15, C16: 1u; C0805
C12, C13: N.C.; C0805
C14: EEEFK1V470P; CAPAE660X610N
C17, C18: 100n; C0603
C19: N.C.; C0603
C20: N.C.; C102-054X133
D5: SKL14; SOD123
D6: N.C.; SOD323-R
IC1: BD00FC0WFP-E2; TO-252-5
IC2: MAX31760AEE+; DBQ16
JP1, JP3, JP4: JP3-CUT-0805-ROTATED; JP3-0805-CUT2
JP2: JP2-NOCUT-0805; JP2-0805-NOCUT
LED1: WP934CB/YD
OK1: N.C.; SO4
Q3: 2N7002; SOT103P240X110-3N; MPN 2N7002-7-F
R5, R7: 39K; R0805
R6: 470R; R0805
R8, R9: 3K3; R0805
R10, R11, R14: 1K; R0805
R12, R15: 4K7; R0805
R13: 10R; R0805
R16, R17, R18, R19: N.C.; R0805
X3: DS1013-16SSIB1; IDC-16PIN
X4: 47053-1000
X5: N.C.; 47053-1000
ZD2, ZD3: N.C.; SOD123

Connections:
12V_PWM: C14.1 (+), IC1.4 (VO), JP1.NC, R5.1
+3V3: C15.2, C17.2, IC2.4 (A1), IC2.5 (A2), IC2.16 (VDD), JP3.NC, JP4.NO, R10.2, R11.2, R12.2, R15.2, R16.2, R18.1, X3.16
+5V: LED1.A, R7.1; also elsewhere on the board
+12V: C12.1, IC1.1 (EN), IC1.2 (VCC), JP1.NO; also elsewhere on the board
AC_L_OUT: C20.1; also elsewhere on the board
AC_N_OUT: D6.C, OK1.1 (A); also elsewhere on the board
FAN_OUT+: C11.1, C13.1, D5.C, JP1.COM, X4.2, X5.2
FAN_OUT-: C11.2, C13.2, JP2.2, X4.1, X5.1
FAN_SENSE1: R10.1, R13.2, X4.3, ZD3.C
FAN_SENSE2: R11.1, R17.2, X5.3, ZD2.C
GND: C12.2, C14.2 (-), C15.1, C16.2, C17.1, C18.2, C19.2, D5.A, IC1.3 (GND), IC2.8 (GND), JP2.1, JP3.NO, OK1.3 (EMIT), Q3.2 (S), R9.2, ZD2.A, ZD3.A; also elsewhere on the board
LDO_FB: IC1.5 (FB), R5.2, R8.1, R9.1
unnamed: C18.1, IC2.7 (TACH1), R13.1
unnamed: IC2.12 (!FF!/!FS!), R16.1
unnamed: JP4.COM, R14.1
unnamed: C16.1, JP4.NC, R8.2
unnamed: D6.A, OK1.2 (C), R19.2
unnamed: Q3.3 (D), R6.2
unnamed: LED1.C, R6.1
unnamed: IC2.11 (!SHDN), R15.1
unnamed: OK1.4 (COL), R18.2, X3.2
unnamed: C20.2, R19.1
unnamed: C19.1, IC2.9 (TACH2), R17.1
unnamed: IC2.3 (A0), JP3.COM
NFAULT: IC2.13 (!ALERT), X3.15
PWM_OUT: IC2.6 (PWM), R12.1, R14.2, X4.4, X5.4
PWR_DIR_OUT: Q3.1 (G), R7.2; also elsewhere on the board
SSCL: IC2.15 (SCL), X3.13
SSDA: IC2.14 (SDA), X3.14

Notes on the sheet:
Licensed under the TAPR Open Hardware License (www.tapr.org/OHL)
Repository: https://github.com/eez-open
More info at https://www.envox.hr/eez
Fan controller with LDO Standby indicator
Standby mode indication
Mains frequency (optional)
12V DC Fan speed controllers

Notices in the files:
parts and their libraries:
EEZ_DIB: This work is licensed under the TAPR Open Hardware License.
COPYRIGHT: Copyright C 2016 Accelerated Designs. All rights reserved
